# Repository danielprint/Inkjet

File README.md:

Inkjet
======

Heated inkjet design

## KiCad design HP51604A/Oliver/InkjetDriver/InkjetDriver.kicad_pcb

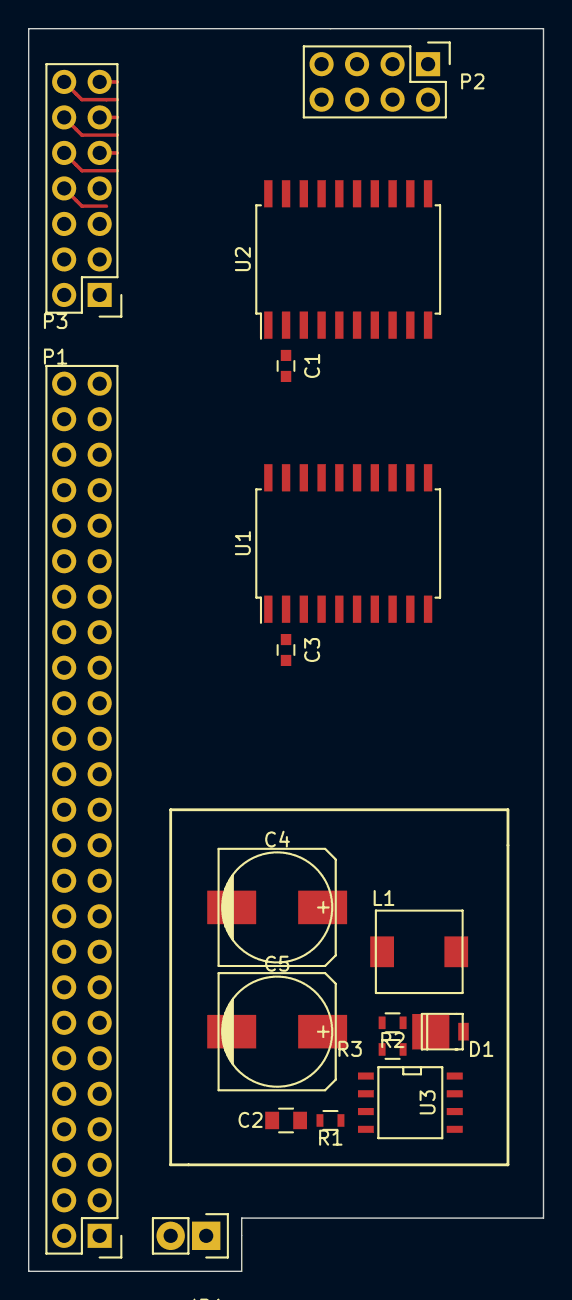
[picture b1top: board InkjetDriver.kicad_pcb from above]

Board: 2 copper layers, 36.8 x 88.9 mm, 17 parts (0 on the bottom side), 27 nets.

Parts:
C1, C3: 0.1uF; C_0603
C2: 1uF; C_0805
C4, C5: 100uF; c_elec_8x10.5
D1: SS3P4; DO-220_Diode
JP1: 12V_EN; Socket_Strip_Straight_1x02
L1: 220uH; CLF6045_Inductor
P1: EXPANSION_HEADER; Pin_Header_Straight_2x25
P2: PWR; Pin_Header_Straight_2x04
P3: INKJET; Pin_Header_Straight_2x07
R1: 1k; R_0603
R2, R3: R; R_0603
U1, U2: 6B595; SOIC-20_7.5x12.8mm_Pitch1.27mm
U3: LT1072; SOIC-8-N

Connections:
19V: C4.1, C5.1, D1.1, P2.2, P2.4, P3.2, R2.1
+5V: C1.1, C3.1, P1.1, U1.2, U2.2
+12V: JP1.1, L1.1, P2.6, P2.8, U3.5
GND: C1.2, C2.2, C3.2, C4.2, C5.2, P1.2, P2.1, P2.3, P2.5, P2.7, R3.2, U1.10, U1.11, U1.19, U2.10, U2.11, U2.19, U3.1, U3.6, U3.8
unnamed: C2.1, R1.2
unnamed: D1.2, L1.2, U3.7
unnamed: JP1.2, P1.4
unnamed: P1.25, U1.8, U2.8
unnamed: P1.31, U1.9, U2.9
unnamed: P1.32, U1.12, U2.12
unnamed: P1.35, U1.13, U2.13
unnamed: P1.40, U1.3
unnamed: P3.3, U1.5
unnamed: P3.4, U1.4
unnamed: P3.5, U1.7
unnamed: P3.6, U1.6
unnamed: P3.7, U1.15
unnamed: P3.8, U1.14
unnamed: P3.9, U1.17
unnamed: P3.10, U1.16
unnamed: P3.11, U2.5
unnamed: P3.12, U2.4
unnamed: P3.13, U2.7
unnamed: P3.14, U2.6
unnamed: R1.1, U3.2
unnamed: R2.2, R3.1, U3.3
unnamed: U1.18, U2.3

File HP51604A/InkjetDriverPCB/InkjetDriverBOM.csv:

Reference, Value, Footprint, Datasheet
U2,6B595,Housings_SOIC:SOIC-20_7.5x12.8mm_Pitch1.27mm,
U1,6B595,Housings_SOIC:SOIC-20_7.5x12.8mm_Pitch1.27mm,
P3,INKJET,Pin_Headers:Pin_Header_Straight_2x07,
C1,0.1uF,Capacitors_SMD:C_0603,
P1,EXPANSION_HEADER,Pin_Headers:Pin_Header_Straight_2x25,
C3,0.1uF,Capacitors_SMD:C_0603,
U3,LT1072,SMD_Packages:SOIC-8-N,
L1,220uH,InkJetPart:CLF6045_Inductor,
D1,SS3P4,InkJetPart:DO-220_Diode,
R2,18.7k 0.1%,Resistors_SMD:R_0603,
R3,1.27k 0.1%,Resistors_SMD:R_0603,
R1,1k,Resistors_SMD:R_0603,
C2,1uF,Capacitors_SMD:C_0805,
C4,100uF,Capacitors_SMD:c_elec_6.3x7.7,
P2,PWR,InkJetPart:Pin_Header_Straight_2x04_Silk_Change,
C5,100uF,Capacitors_SMD:c_elec_6.3x7.7,
JP1,PWR_SELECT,Socket_Strips:Socket_Strip_Straight_1x03,

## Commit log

2013-12-24 First commit.
2013-12-25 Better insert design.
2014-09-24 Designs for HP51604A head added.
2014-11-24 Amberish's report added.
2015-07-06 Oliver's designs added.
2015-07-07 Step files for HP inkjet holder added, and photos of it.
2015-07-09 Updating the Inkjet repository with all Oliver's files. There may be some duplicates that need to be sorted out.
2015-07-13 'Inkjet driver PCB files added'
2015-07-13 Interface PCB changed to allow 19V supply to be routed past the buck converter.
2015-07-13 Fixed (I think) the component numbers in the inkjet driver.
2015-07-14 Bill of materials added
2015-07-20 Bringing files up to date
2015-07-20 Screw-hole lugs added to horizontal mount.
2015-07-20 Instructions and BOM added
2015-07-20 Horizontal mount slot expanded to accommodate PCB.
2015-09-04 Update on the day of Oliver's leaving - all his latest files.
2015-09-08 Added FreeCAD versions.
2015-11-16 SVG solder mask added.
